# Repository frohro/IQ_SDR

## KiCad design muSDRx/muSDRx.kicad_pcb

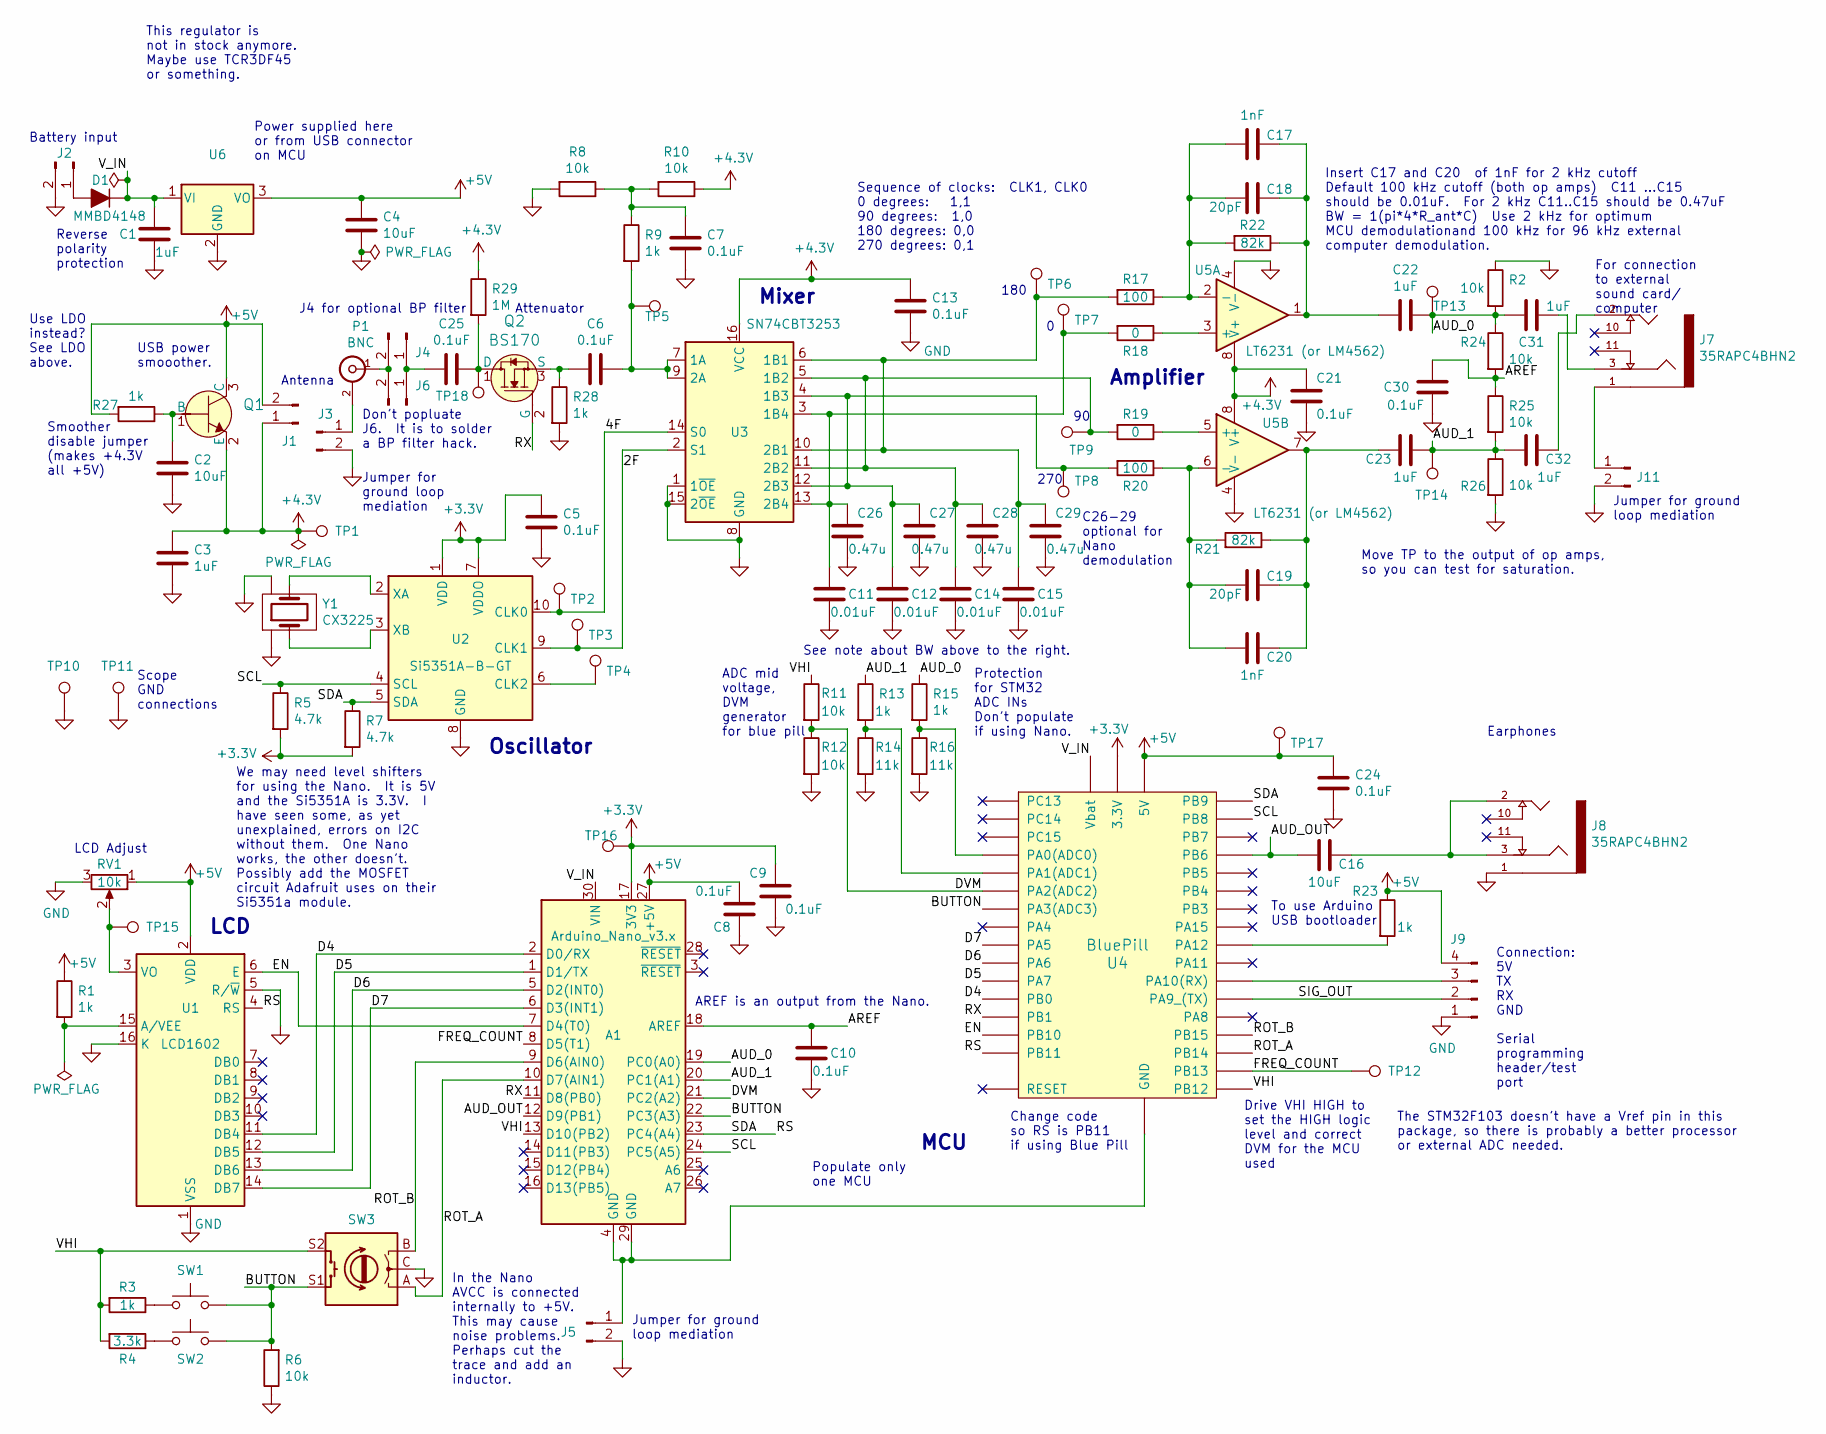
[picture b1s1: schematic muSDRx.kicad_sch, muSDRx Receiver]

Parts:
A1: Arduino_Nano_v3.x; Arduino_Nano
C1, C3, C22, C23: 1uF; C_0805
C2, C4, C16: 10uF; C_0805
C5, C6, C7, C8, C9, C10, C13, C21, C24: 0.1uF; C_0805
C11, C12, C14, C15: 0.01uF; C_0805
C17, C20: 1nF; C_0805_2012Metric
C18, C19: 20pF; C_0805
C25, C30: 0.1uF; C_0805_2012Metric
C26, C27, C28, C29: 0.47u; C_0805_2012Metric
C31, C32: 1uF; C_0805_2012Metric
D1: MMBD4148; D_SOT-23_ANK
J1, J2, J3, J4, J5, J6, J11: Conn_01x02_Male; Pin_Header_Straight_1x02_Pitch2.54mm
J7, J8: 35RAPC4BHN2; SWITCHCRAFT_35RAPC4BHN2
J9: Conn_01x04_Male; Pin_Header_Straight_1x04_Pitch2.54mm
P1: BNC; BNC_Socket_TYCO-AMP_LargePads
Q1: MMBT2222A-TP; SOT-23-3; MPN MMBT2222A-TP; Digi-Key_PN MMBT2222ATPMSCT-ND
Q2: BS170; TO-92-3; MPN BS170; Digi-Key_PN BS170-ND
R1, R3, R9, R13, R15, R23: 1k; R_0805
R2, R24, R25, R26: 10k; R_0805_2012Metric
R4: 3.3k; R_0805
R5, R7: 4.7k; R_0805
R6, R8, R10, R11, R12: 10k; R_0805
R14, R16: 11k; R_0805
R17, R20: 100; R_0805
R18, R19: 0; R_0805
R21, R22: 82k; R_0805
R27, R28: 1k; R_0805_2012Metric
R29: 1M; R_0805_2012Metric
RV1: 10k; Potentiometer_Trimmer_ACP_CA6h_Vertical
SW1, SW2: SW_Push; SW_PUSH_6mm_h4.3mm
SW3: Rotary_Encoder_Switch; Rotary_Encoder_Switched_PEC11R
TP1, TP2, TP3, TP4, TP5, TP6, TP7, TP8, TP9, TP10, TP11, TP12, TP13, TP14, TP15, TP16, TP17: TestPoint; PINTST
TP18: TestPoint; TestPoint_THTPad_D1.5mm_Drill0.7mm
U1: LCD1602; Pin_Header_Straight_1x16_Pitch2.54mm
U2: Si5351A-B-GT; MSOP-10_3x3mm_Pitch0.5mm
U3: SN74CBT3253; SOIC-16_3.9x9.9mm_Pitch1.27mm
U4: BluePill; BLUEPILL
U5: LT6231 (or LM4562); SOIC-8_3.9x4.9mm_Pitch1.27mm
U6: (no value)
Y1: CX3225; Crystal_SMD_Abracon_ABM8G-4pin_3.2x2.5mm

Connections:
+3V3: A1.17 (3V3), C5.1, C9.1, R5.2, R7.2, TP16.1, U2.1 (VDD), U2.7 (VDDO), U4.3V3 (3.3V)
+4.3V: C3.1, C13.1, C21.1, J1.1, Q1.2 (E), R10.1, R29.1, TP1.1, U3.16 (VCC), U5.8 (V+)
+5V: A1.27 (+5V), C4.1, C8.1, C24.1, J1.2, J9.4, Q1.3 (C), R1.1, R23.1, R27.2, RV1.1, TP17.1, U1.2 (VDD), U4.5V, U6.3 (VO)
/2F: TP3.1, U2.9 (CLK1), U3.2 (S1)
/4F: TP2.1, U2.10 (CLK0), U3.14 (S0)
/AREF: A1.18 (AREF), C10.1, C30.2, R24.2, R25.1
/AUD_0: A1.19 (PC0(A0)), C22.1, C31.1, R2.2, R15.1, R24.1, TP13.1
/AUD_1: A1.20 (PC1(A1)), C23.1, C32.1, R13.1, R25.2, R26.1, TP14.1
/AUD_OUT: A1.12 (D9(PB1)), C16.2, U4.PB6
/BUTTON: A1.22 (PC3(A3)), R6.2, SW1.2, SW2.2, SW3.S1, U4.PA3 (PA3(ADC3))
/D4: A1.2 (D0/RX), U1.11 (DB4), U4.PB0
/D5: A1.1 (D1/TX), U1.12 (DB5), U4.PA7
/D6: A1.5 (D2(INT0)), U1.13 (DB6), U4.PA6
/D7: A1.6 (D3(INT1)), U1.14 (DB7), U4.PA5
/DVM: A1.21 (PC2(A2)), R11.2, R12.1, U4.PA2 (PA2(ADC2))
/EN: A1.7 (D4(T0)), U1.6 (E), U4.PB10
/FREQ_COUNT: A1.8 (D5(T1)), TP12.1, U4.PB13
/ROT_A: A1.10 (D7(AIN1)), SW3.A, U4.PB14
/ROT_B: A1.9 (D6(AIN0)), SW3.B, U4.PB15
/RS: A1.23 (PC4(A4)), R7.1, U1.4 (RS), U2.5 (SDA), U4.PB9, U4.PB11
/RX: A1.11 (D8(PB0)), Q2.2 (G), U4.PB1
/SCL: A1.24 (PC5(A5)), R5.1, U2.4 (SCL), U4.PB8
/SIG_OUT: J9.2, U4.PA9 (PA9_(TX))
/VHI: A1.13 (D10(PB2)), R3.2, R4.2, R11.1, SW3.S2, U4.PB12
/V_IN: A1.30 (VIN), C1.1, D1.3 (K), U4.VBAT (Vbat), U6.1 (VI)
GND: C1.2, C2.2, C3.2, C4.2, C5.2, C7.2, C8.2, C9.2, C10.2, C11.2, C12.2, C13.2, C14.2, C15.2, C21.2, C24.2, C26.2, C27.2, C28.2, C29.2, C30.1, J2.2, J3.2, J5.2, J8.1, J9.1, J11.2, R2.1, R6.1, R8.2, R12.2, R14.2, R16.2, R26.2, R28.2, RV1.3, SW3.C, TP10.1, TP11.1, U1.1 (VSS), U1.5 (R/~W), U1.16 (K), U2.8 (GND), U3.1 (1~OE), U3.8 (GND), U3.15 (2~OE), U5.4 (V-), U6.2 (GND), Y1.2 (GND), Y1.4 (GND)
unnamed: A1.4 (GND), A1.29 (GND), J5.1, U4.G (GND)
unnamed: C2.1, Q1.1 (B), R27.1
unnamed: C6.1, R9.2, TP5.1, U3.7 (1A), U3.9 (2A)
unnamed: C6.2, Q2.3 (S), R28.1
unnamed: C7.1, R8.1, R9.1, R10.2
unnamed: C11.1, C26.1, R18.2, TP7.1, U3.3 (1B4), U3.13 (2B4)
unnamed: C12.1, C27.1, R20.2, TP8.1, U3.4 (1B3), U3.12 (2B3)
unnamed: C14.1, C28.1, R19.2, TP9.1, U3.5 (1B2), U3.11 (2B2)
unnamed: C15.1, C29.1, R17.2, TP6.1, U3.6 (1B1), U3.10 (2B1)
unnamed: C16.1, J8.2, J8.3
unnamed: C17.1, C18.1, C22.2, R22.1, U5.1
unnamed: C17.2, C18.2, R17.1, R22.2, U5.2 (-)
unnamed: C19.1, C20.1, C23.2, R21.1, U5.7
unnamed: C19.2, C20.2, R20.1, R21.2, U5.6 (-)
unnamed: C25.1, Q2.1 (D), R29.2, TP18.1
unnamed: C25.2, J4.1, J6.1
unnamed: C31.2, J7.3
unnamed: C32.2, J7.2
unnamed: D1.1 (A), J2.1
unnamed: J3.1, P1.2 (Ext)
unnamed: J4.2, J6.2, P1.1 (In)
unnamed: J9.3, U4.PA10 (PA10(RX))
unnamed: J7.1, J11.1
unnamed: R1.2, U1.15 (A/VEE)
unnamed: R3.1, SW1.1
unnamed: R4.1, SW2.1
unnamed: R13.2, R14.1, U4.PA1 (PA1(ADC1))
unnamed: R15.2, R16.1, U4.PA0 (PA0(ADC0))
unnamed: R18.1, U5.3 (+)
unnamed: R19.1, U5.5 (+)
unnamed: R23.2, U4.PA12
unnamed: RV1.2, TP15.1, U1.3 (VO)
unnamed: TP4.1, U2.6 (CLK2)
unnamed: U2.2 (XA), Y1.3 (2)
unnamed: U2.3 (XB), Y1.1

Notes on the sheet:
Power supplied here or from USB connector on MCU
Jumper for ground loop mediation
Reverse polarity protection
J4 for optional BP filter
Scope GND connections
Earphones
ADC mid voltage, DVM generator for blue pill
180
Populate only one MCU
Serial programming header/test port
C26-29 optional for Nano demodulation
Attenuator
Don't popluate J6. It is to solder a BP filter hack.
Mixer
Battery input
Amplifier
270
Jumper for ground loop mediation
USB power smooother.
Change code so RS is PB11 if using Blue Pill
Sequence of clocks: CLK1, CLK0 0 degrees: 1,1 90 degrees: 1,0 180 degrees: 0,0 270 degrees: 0,1
Use LDO instead? See LDO above.
Antenna
For connection to external sound card/ computer
See note about BW above to the right.
This regulator is not in stock anymore. Maybe use TCR3DF45 or something.
Move TP to the output of op amps, so you can test for saturation.
LCD
In the Nano AVCC is connected internally to +5V. This may cause noise problems. Perhaps cut the trace and add an inductor.
To use Arduino USB bootloader
Smoother disable jumper (makes +4.3V all +5V)
The STM32F103 doesn't have a Vref pin in this package, so there is probably a better processor or external ADC needed.
Protection for STM32 ADC INs Don't populate if using Nano.
AREF is an output from the Nano.
Insert C17 and C20 of 1nF for 2 kHz cutoff Default 100 kHz cutoff (both op amps) C11 ...C15 should be 0.01uF. For 2 kHz C11..C15 should be 0.47uF BW = 1(pi*4*R_ant*C) Use 2 kHz for optimum MCU demodulationand 100 kHz for 96 kHz external computer demodulation.
MCU
Oscillator
Drive VHI HIGH to set the HIGH logic level and correct DVM for the MCU used
We may need level shifters for using the Nano. It is 5V and the Si5351A is 3.3V. I have seen some, as yet unexplained, errors on I2C without them. One Nano works, the other doesn't. Possibly add the MOSFET circuit Adafruit uses on their Si5351a module.
LCD Adjust

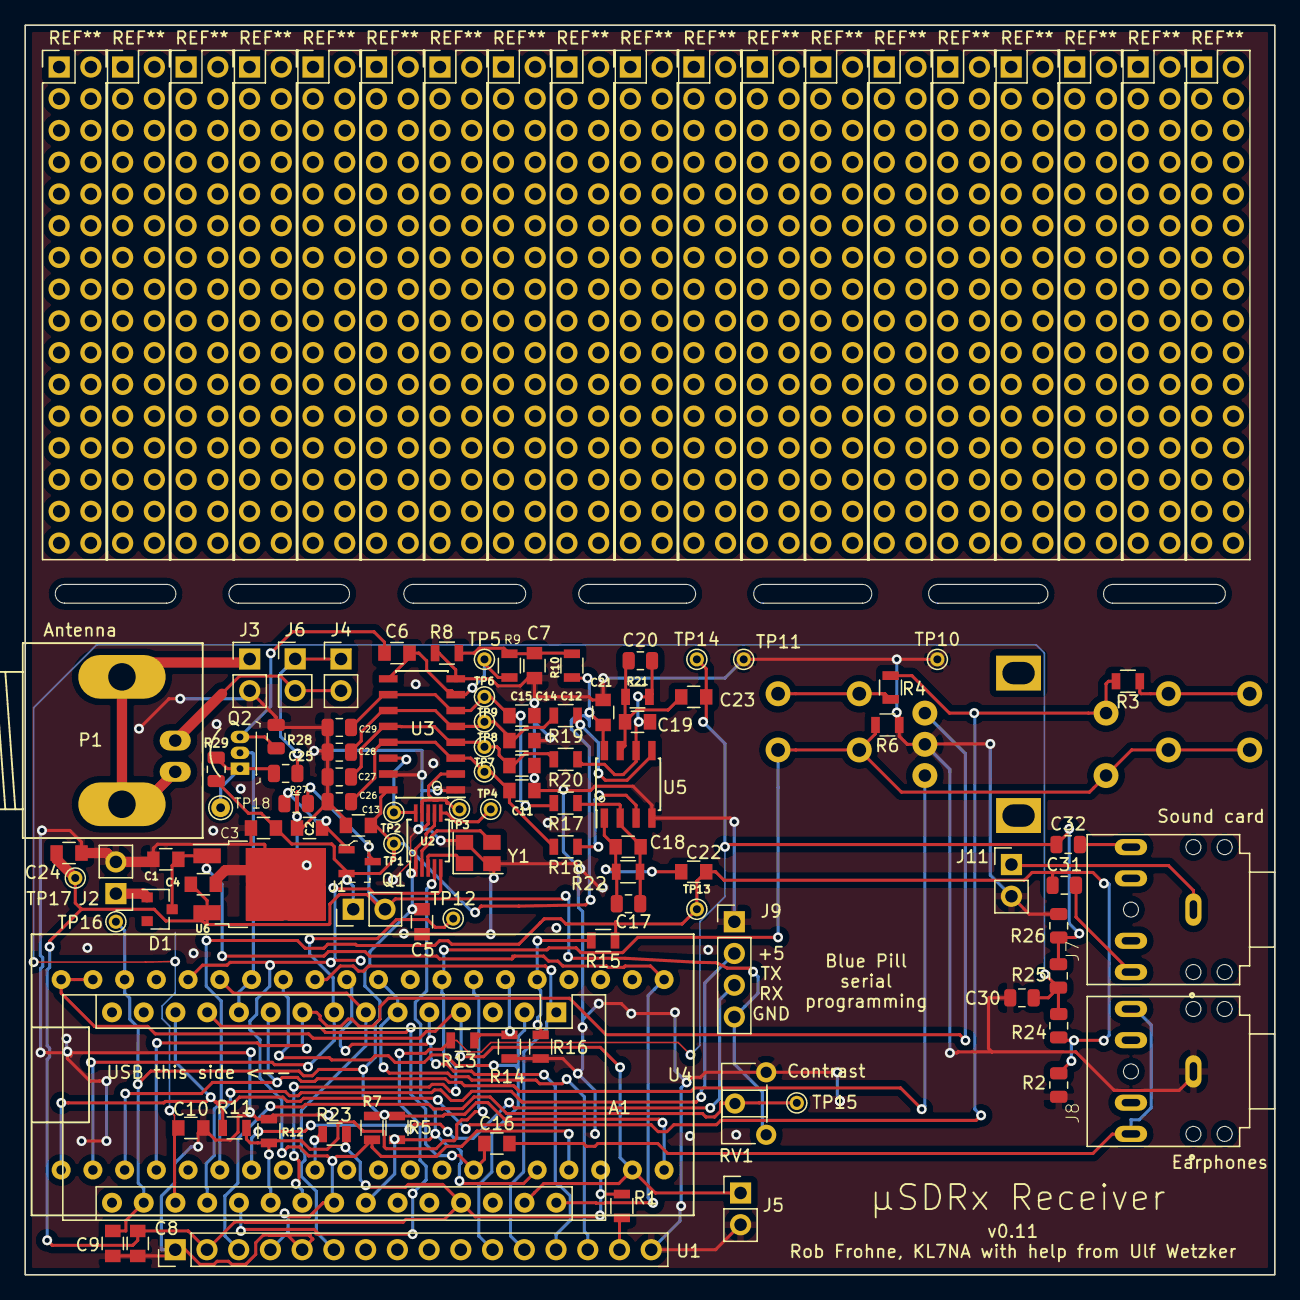
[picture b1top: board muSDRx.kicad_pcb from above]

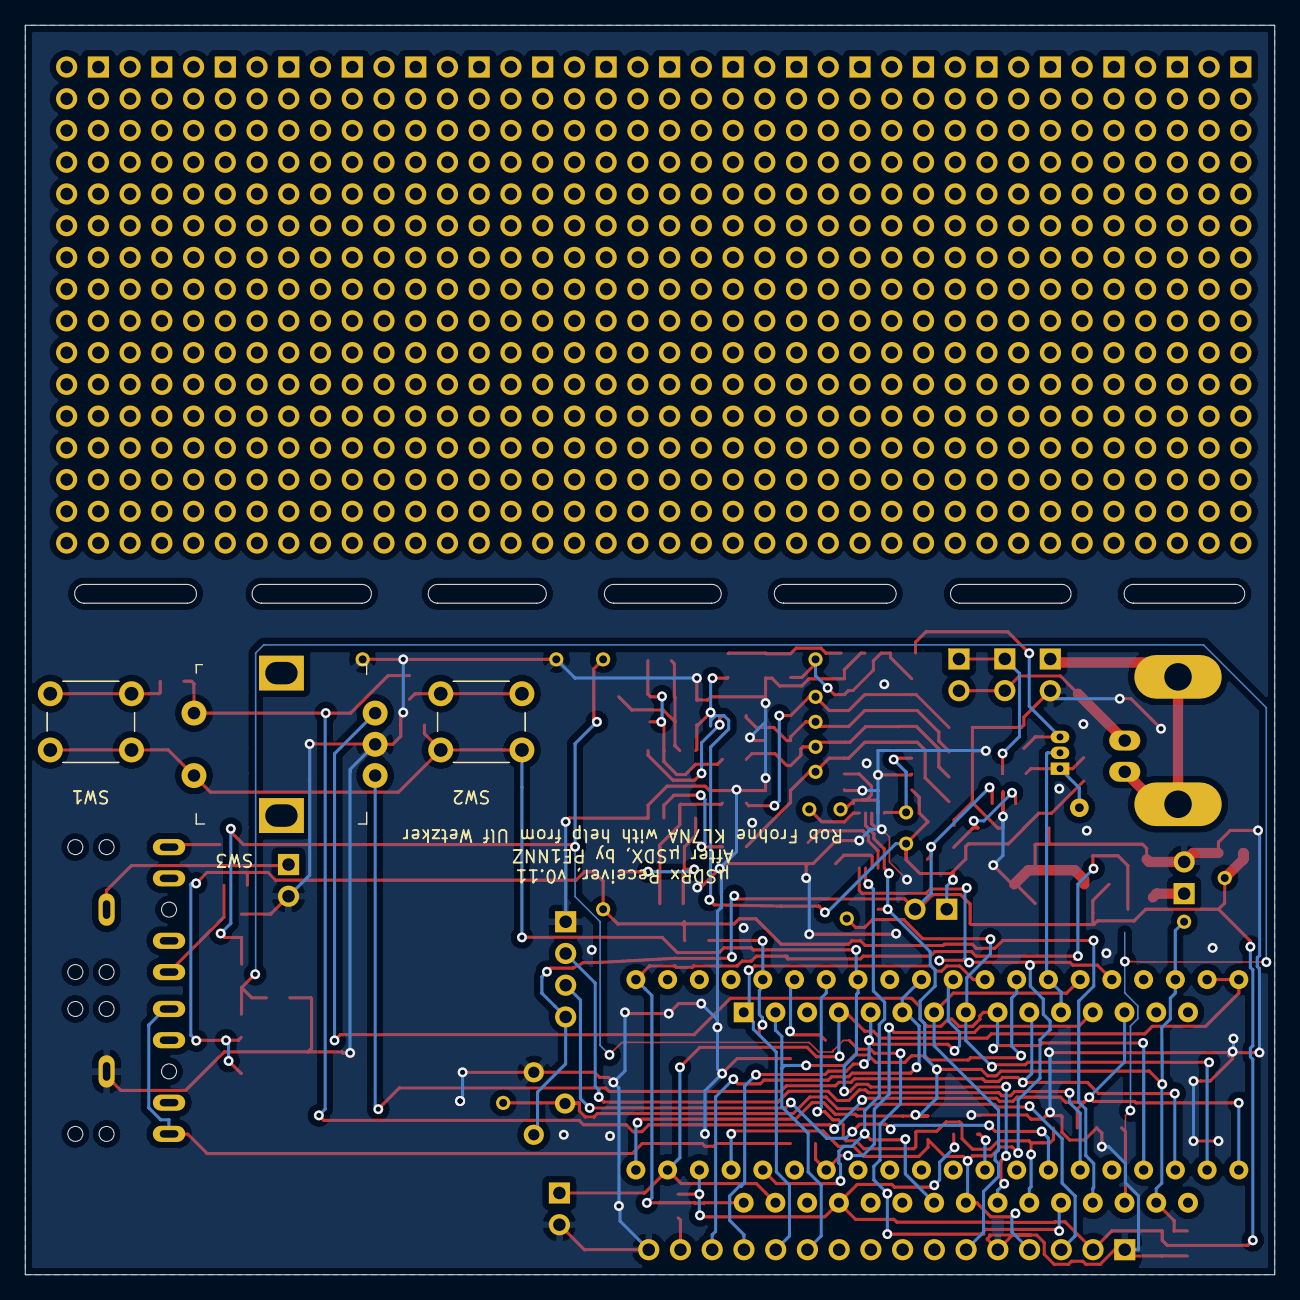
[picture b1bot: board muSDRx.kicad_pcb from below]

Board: 2 copper layers, 100.0 x 100.0 mm, 105 parts (3 on the bottom side), 61 nets.

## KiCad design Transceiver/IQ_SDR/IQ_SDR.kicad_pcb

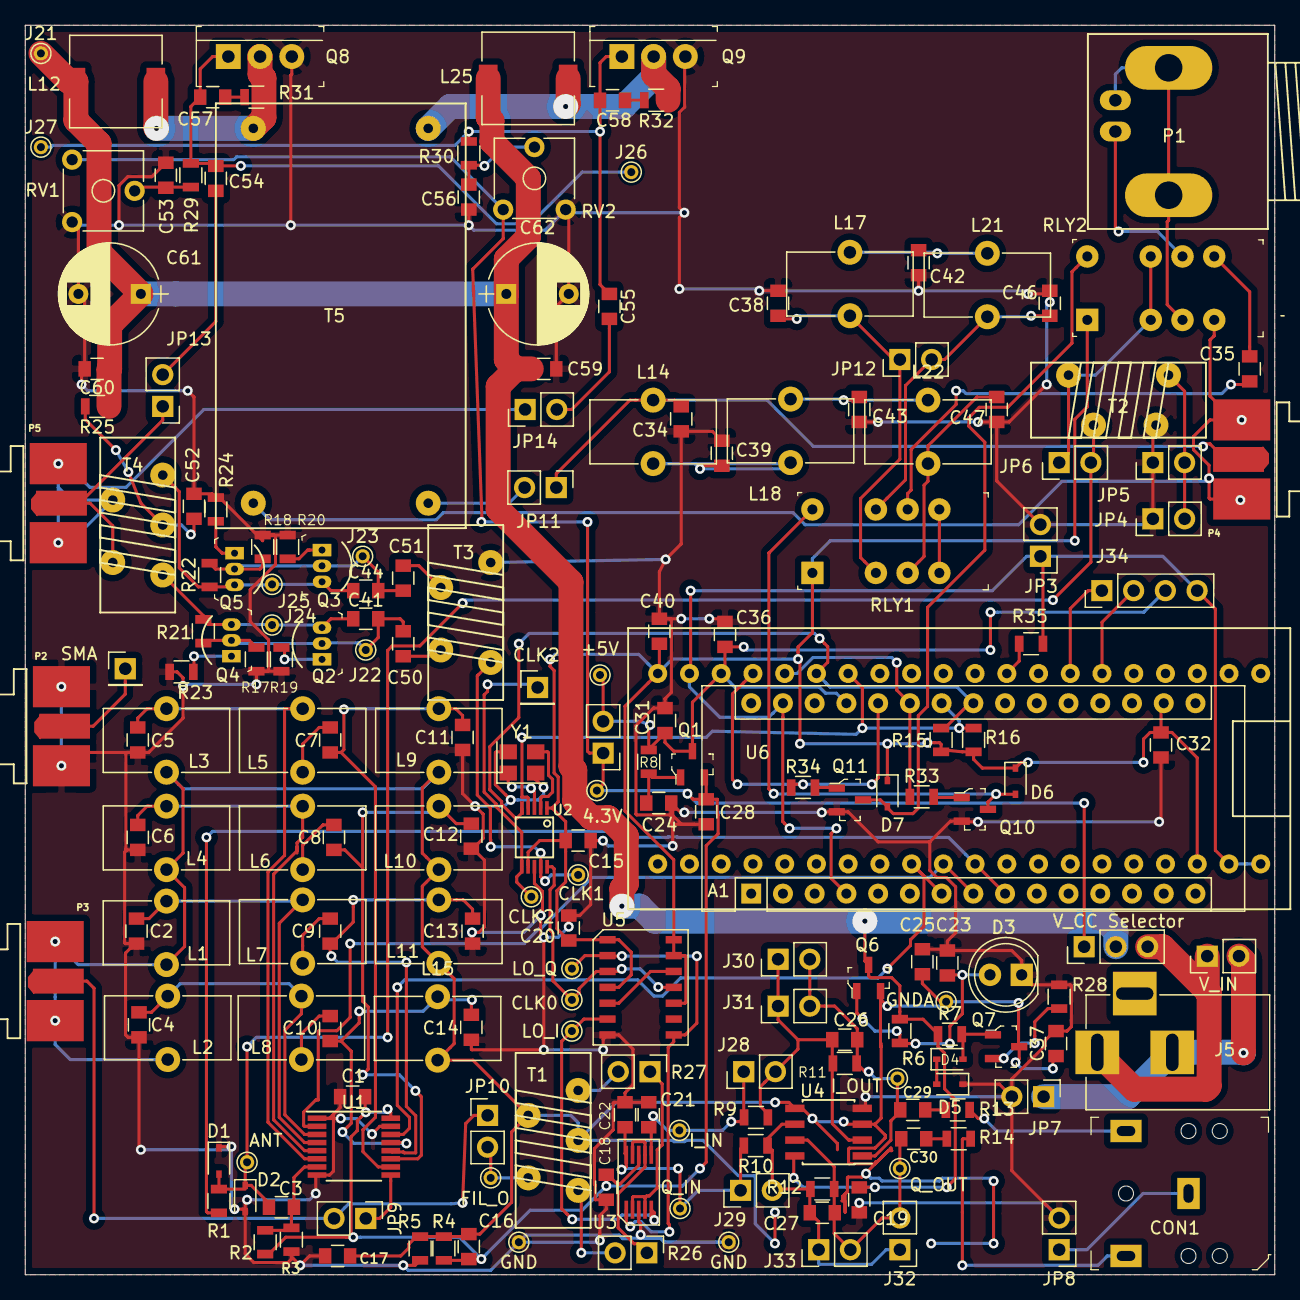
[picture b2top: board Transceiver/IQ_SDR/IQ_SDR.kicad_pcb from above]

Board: 2 copper layers, 100.0 x 100.0 mm, 201 parts (0 on the bottom side), 108 nets.

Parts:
A1: Arduino_Nano_v3.x; Arduino_Nano
C1, C18, C19: 0.01; C_0805
C2, C13: 820pF; C_0805
C3, C15, C16, C17, C20, C25, C28, C32, C40, C50, C51, C52, C53, C54, C55, C56, C57, C58, C59, C60: 0.1uF; C_0805
C4, C14: 1.5nF; C_0805
C5, C11, C41, C44: 220pF; C_0805
C6, C12: 390pF; C_0805
C7: 47pF; C_0805
C8: 100pF; C_0805
C9, C46: 180pF; C_0805
C10: 470pF; C_0805
C21, C22: 0.02uF; C_0805
C23, C24, C29, C30, C31, C36: 10uF; C_0805
C26, C27: 50pF; C_0805
C34, C47: 82pF; C_0805
C35: 1uF; C_0805
C37: 1u; C_0805
C38: 510pF; C_0805
C39, C43: 330pF; C_0805
C42: 680pF; C_0805
C61, C62: 470uF; CP_Radial_D8.0mm_P5.00mm
CON1: SJ1-3523N; Headphone_Jack_2.5mm_SJ1-3523N
D1, D2, D4, D5, D6, D7: 1N914; D_SOD-323
D3: LED_Solid; LED_D5.0mm
J1: ANT; PINTST
J2, J4: GND; PINTST
J3: V_IN; Pin_Header_Straight_1x02_Pitch2.54mm
J5: V_IN; BARREL_JACK
J6: FIL_O; PINTST
J7: CLK1; PINTST
J8: CLK2; PINTST
J9: CLK0; PINTST
J10: LO_I; PINTST
J11: LO_Q; PINTST
J12: GNDA; PINTST
J13: I_IN; PINTST
J14: Q_IN; PINTST
J15: +5V; PINTST
J16: 4.3V; PINTST
J17: I_OUT; PINTST
J18: Q_OUT; PINTST
J19: CLK2; Pin_Header_Straight_1x01_Pitch2.54mm
J20: SMA; Pin_Header_Straight_1x01_Pitch2.54mm
J21: V_CC; PINTST
J22: Ba; PINTST
J23: Bb; PINTST
J24: Cb; PINTST
J25: Ca; PINTST
J26: Gb; PINTST
J27: Ga; PINTST
J28, J29, J30, J31, J32, J33: Conn_01x02_Female; Socket_Strip_Straight_1x02_Pitch2.54mm
J34: Conn_01x04_Male; Pin_Header_Straight_1x04_Pitch2.54mm
JP1: smooth disable; Pin_Header_Straight_1x02_Pitch2.54mm
JP2: V_CC Selector; Pin_Header_Straight_1x03_Pitch2.54mm
JP3: Ground loop mitigation for the Arduino; Pin_Header_Straight_1x02_Pitch2.54mm
JP4: Ground loop mitigation for the RX antenna; Pin_Header_Straight_1x02_Pitch2.54mm
JP5, JP6: T2 bypass; Pin_Header_Straight_1x02_Pitch2.54mm
JP7: V_IN ground loop mitigation; Pin_Header_Straight_1x02_Pitch2.54mm
JP8: Ground loop mitigation for audio; Pin_Header_Straight_1x02_Pitch2.54mm
JP9: BP_1; Pin_Header_Straight_1x02_Pitch2.54mm
JP10: BP_2; Pin_Header_Straight_1x02_Pitch2.54mm
JP11: Tx filter disconnect; Pin_Header_Straight_1x02_Pitch2.54mm
JP12: 40m Filter Bypass; Pin_Header_Straight_1x02_Pitch2.54mm
JP13, JP14: QRP; Pin_Header_Straight_1x02_Pitch2.54mm
L1: 1uH; L_Toroid_Vertical_L10.0mm_W5.0mm_P5.08mm
L2, L15: 2.4uH; L_Toroid_Vertical_L10.0mm_W5.0mm_P5.08mm
L3: 232nH; L_Toroid_Vertical_L10.0mm_W5.0mm_P5.08mm
L4: 497nH; L_Toroid_Vertical_L10.0mm_W5.0mm_P5.08mm
L5: 1.137uH; L_Toroid_Vertical_L10.0mm_W5.0mm_P5.08mm
L6: 1.98uH; L_Toroid_Vertical_L10.0mm_W5.0mm_P5.08mm
L7: 4uH; L_Toroid_Vertical_L10.0mm_W5.0mm_P5.08mm
L8: 7.2uH; L_Toroid_Vertical_L10.0mm_W5.0mm_P5.08mm
L9: 256nH; L_Toroid_Vertical_L10.0mm_W5.0mm_P5.08mm
L10: 626nH; L_Toroid_Vertical_L10.0mm_W5.0mm_P5.08mm
L11, L17: 1.7uH; L_Toroid_Vertical_L10.0mm_W5.0mm_P5.08mm
L12, L25: 300uH; L_7.3x7.3_H4.5
L14, L22: 590nH; L_Toroid_Vertical_L10.0mm_W5.0mm_P5.08mm
L18: 910nH; L_Toroid_Vertical_L10.0mm_W5.0mm_P5.08mm
L21: 1.24uH; L_Toroid_Vertical_L10.0mm_W5.0mm_P5.08mm
P1: BNC; BNC_Socket_TYCO-AMP_LargePads
P2, P3, P4, P5: SMA; SMA_EDGE
Q1, Q6, Q7, Q10, Q11: MMBT2222A-TP; SOT-23-3
Q2, Q3, Q4, Q5: 2N3904; TO-92-3
Q8, Q9: IRF510PBF; TO-220-3
R1: 2.2k; R_0805
R2, R4: 10k; R_0805
R3, R5: 5.6k; R_0805
R6: 2k; R_0805
R7: 27k; R_0805
R8, R21, R22: 1k; R_0805
R9, R10: 50; R_0805
R11, R12: 13k; R_0805
R13, R14, R17, R18: 100; R_0805
R15, R16, R33, R34: 4.7k; R_0805
R19, R20, R23, R24: 22; R_0805
R25: 2.2; R_0805
R26, R27: 0; Socket_Strip_Straight_1x02_Pitch2.54mm
R28: 500; R_0805
R29, R30: 47; R_0805
R31, R32: 220; R_0805
R35: 1.6k; R_0805
RLY1, RLY2: TX2SA-L-3V-Z
RV1, RV2: 10k; Potentiometer_Trimmer_ACP_CA6v_Horizontal
T1: Transformer_1P_SS; T50-2_vertical_5_pin
T2, T3: Transformer_1P_1S; T50-2_vertical_4_pin
T4: Transformer_SP_1S; T50-2_vertical_5_pin
T5: BN43-6802
U1: FST3253 or TS3A5017; TSSOP-16_4.4x5mm_Pitch0.65mm
U2: Si5351A-B-GT; MSOP-10
U3: TS5A23157; DGS0010A
U4: LM4562 or LT6231; SOIC-8_3.9x4.9mm_Pitch1.27mm
U5: 74ALVC74D; SO14
U6: Blue Pill; BLUEPILL
Y1: CX3225; Crystal_SMD_Abracon_ABM8G-4pin_3.2x2.5mm

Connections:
+3V3: A1.17, C15.1, C20.1, C32.1, C40.1, D6.1, D7.1, R15.2, R16.2, RLY1.1, RLY2.1, U2.1, U2.7, U5.1, U5.4, U5.10, U5.13, U5.14, U6.3V3
+4.3V: C1.1, C16.1, C18.1, C28.1, J16.1, JP1.1, JP2.1, Q1.2, R2.2, R4.2, RV1.3, RV2.3, U1.16, U3.8
+5V: A1.27, C31.1, C36.1, J15.1, J34.3, JP1.2, Q1.3, R8.1, U6.5V
/ANT_RLY: A1.26, R34.1, U6.PB9
/B0: A1.7, U1.14, U6.PA4
/B1: A1.8, U1.2, U6.PA5
/D_GND: A1.4, A1.29, J34.4, JP3.1, R35.2, U6.G
/LO_I: J10.1, U3.5, U5.6
/LO_Q: J11.1, U3.1, U5.2, U5.8
/MUTE: A1.9, R1.2, U6.PA6
/PA_V_CCb: L12.1, Q8.2, R31.1, T5.1
/PA_V_CCc: L25.1, Q9.2, R32.1, T5.2
/RFa: P4.2, RLY2.5, T5.3
/RFb: P1.2, RLY2.4
/RFc: C35.2, RLY1.9
/RFd: C47.1, L22.2, RLY1.4
/RFf: C39.1, L14.2, L18.1
/RFg: C38.1, JP12.1, L17.1, RLY1.3
/RFh: C46.1, JP12.2, L21.2, RLY1.10
/RFj: C43.1, L18.2, L22.1
/RFk: C42.1, L17.2, L21.1
/RFm: P1.1, RLY2.9
/RX_ANT_+: JP6.1, RLY2.3, RLY2.10, T2.1
/RX_ANT_-: JP4.2, JP5.2, T2.2
/Rfe: C34.1, JP11.1, L14.1, P4.1
/SCL: A1.24, R16.1, U2.4, U6.PB6
/SDA: A1.23, R15.1, U2.5, U6.PB7
/TX_BAND: A1.25, R33.1, U6.PB8
GND: C1.2, C2.2, C4.2, C5.2, C6.2, C11.2, C12.2, C13.2, C14.2, C15.2, C17.2, C18.2, C19.2, C20.2, C21.2, C22.2, C23.1, C24.2, C25.1, C28.2, C31.2, C32.2, C34.2, C36.2, C37.2, C38.2, C39.2, C40.2, C42.2, C43.2, C46.2, C47.2, C52.2, C53.2, C56.2, C59.2, C60.2, C61.2, C62.2, D1.1, D2.2, D3.1, D5.1, J2.1, J4.1, JP3.2, JP4.1, JP5.1, JP7.2, JP8.2, P2.2, Q8.3, Q9.3, Q10.2, Q11.2, R3.1, R5.1, R17.2, R18.2, R19.2, R20.2, R23.2, R24.2, R28.2, RV1.1, RV2.1, T2.3, T3.1, U1.1, U1.8, U1.15, U2.8, U3.3, U4.4, U5.7, Y1.2, Y1.4
GNDA: C16.2, C17.1, C25.2, C37.1, J12.1, L1.2, L2.2, L3.2, L4.2, L9.2, L10.2, L11.2, L15.2, P3.2, Q6.2, Q7.3, R4.1, R5.2, T1.1, T1.4, U4.3, U4.5
unnamed: C2.1, L1.1, L7.1, U1.4
unnamed: C3.1, D1.2, D2.1, J1.1, JP6.2, R1.1, T2.4
unnamed: C3.2, R2.1, R3.2, U1.7
unnamed: C4.1, L2.1, L8.1, U1.3
unnamed: C5.1, L3.1, L5.1, U1.6
unnamed: C6.1, L4.1, L6.1, U1.5
unnamed: C7.2, L5.2
unnamed: C8.2, L6.2
unnamed: C9.2, L7.2
unnamed: C10.1, C14.1, L15.1, U1.13
unnamed: C10.2, L8.2
unnamed: C7.1, C11.1, L9.1, U1.10
unnamed: C8.1, C12.1, L10.1, U1.11
unnamed: C9.1, C13.1, L11.1, U1.12
unnamed: C21.1, J13.1, J28.1, R9.2, U3.6
unnamed: C22.1, J14.1, J29.1, R10.2, U3.10
unnamed: C23.2, D3.2, Q6.1, R6.2
unnamed: C24.1, Q1.1, R8.2
unnamed: C26.1, C29.2, J17.1, J30.2, J31.2, R11.1, U4.1
unnamed: C26.2, J28.2, J30.1, J31.1, R9.1, R11.2, U4.2
unnamed: C27.1, C30.2, J18.1, J32.2, J33.2, R12.1, U4.7
unnamed: C27.2, J29.2, J32.1, J33.1, R10.1, R12.2, U4.6
unnamed: C29.1, R13.2
unnamed: C30.1, R14.2
unnamed: C35.1, RLY2.8
unnamed: C41.1, J24.1, Q2.3, Q4.3, R21.1, T4.3
unnamed: C41.2, C50.1, J22.1, Q2.2, Q4.2, R17.1, R21.2
unnamed: C44.1, J25.1, Q3.3, Q5.3, R22.1, T4.1
unnamed: C44.2, C51.1, J23.1, Q3.2, Q5.2, R18.1, R22.2
unnamed: C50.2, T3.3
unnamed: C51.2, T3.4
unnamed: C52.1, R25.2, T4.2
unnamed: C53.1, R29.1, RV1.2
unnamed: C54.1, C57.1, J26.1, Q8.1, R29.2
unnamed: C54.2, JP13.2
unnamed: C55.1, C58.1, J27.1, Q9.1, R30.2
unnamed: C55.2, JP14.2
unnamed: C56.1, R30.1, RV2.2
unnamed: C57.2, R31.2
unnamed: C58.2, R32.2
unnamed: CON1.1, JP8.1
unnamed: CON1.2, R13.1
unnamed: CON1.3, R14.1
unnamed: D4.1, D5.2
unnamed: D4.2, Q7.1, R7.2
unnamed: D6.2, Q10.3, RLY1.12
unnamed: D7.2, Q11.3, RLY2.12
unnamed: J3.2, J5.2, JP7.1
unnamed: J6.1, JP10.2, T1.2
unnamed: J7.1, T3.2, U2.9
unnamed: J9.1, U2.10, U5.3, U5.11
unnamed: J8.1, J19.1, U2.6
unnamed: J20.1, P2.1
unnamed: J34.1, U6.PA10
unnamed: J34.2, U6.PA9
unnamed: JP9.1, U1.9
unnamed: JP9.2, JP10.1, P3.1
unnamed: JP11.2, T5.4
unnamed: JP13.1, P5.1, T4.4
unnamed: JP14.1, P5.2, T4.5
unnamed: Q2.1, R19.1
unnamed: Q3.1, R20.1
unnamed: Q4.1, R23.1
unnamed: Q5.1, R24.1
unnamed: Q7.2, R28.1
unnamed: Q10.1, R33.2
unnamed: Q11.1, R34.2
unnamed: R26.1, U3.7, U3.9
unnamed: R26.2, T1.3
unnamed: R27.1, U3.2, U3.4
unnamed: R27.2, T1.5
unnamed: R35.1, U6.PA12
unnamed: RLY1.5, RLY1.8
unnamed: U2.2, Y1.3
unnamed: U2.3, Y1.1
unnamed: U5.5, U5.12
V_CC: C19.1, C59.1, C60.1, C61.1, C62.1, J21.1, JP2.2, L12.2, L25.2, Q6.3, R6.1, R7.1, R25.1, U4.8
V_IN: J3.1, J5.1, JP2.3

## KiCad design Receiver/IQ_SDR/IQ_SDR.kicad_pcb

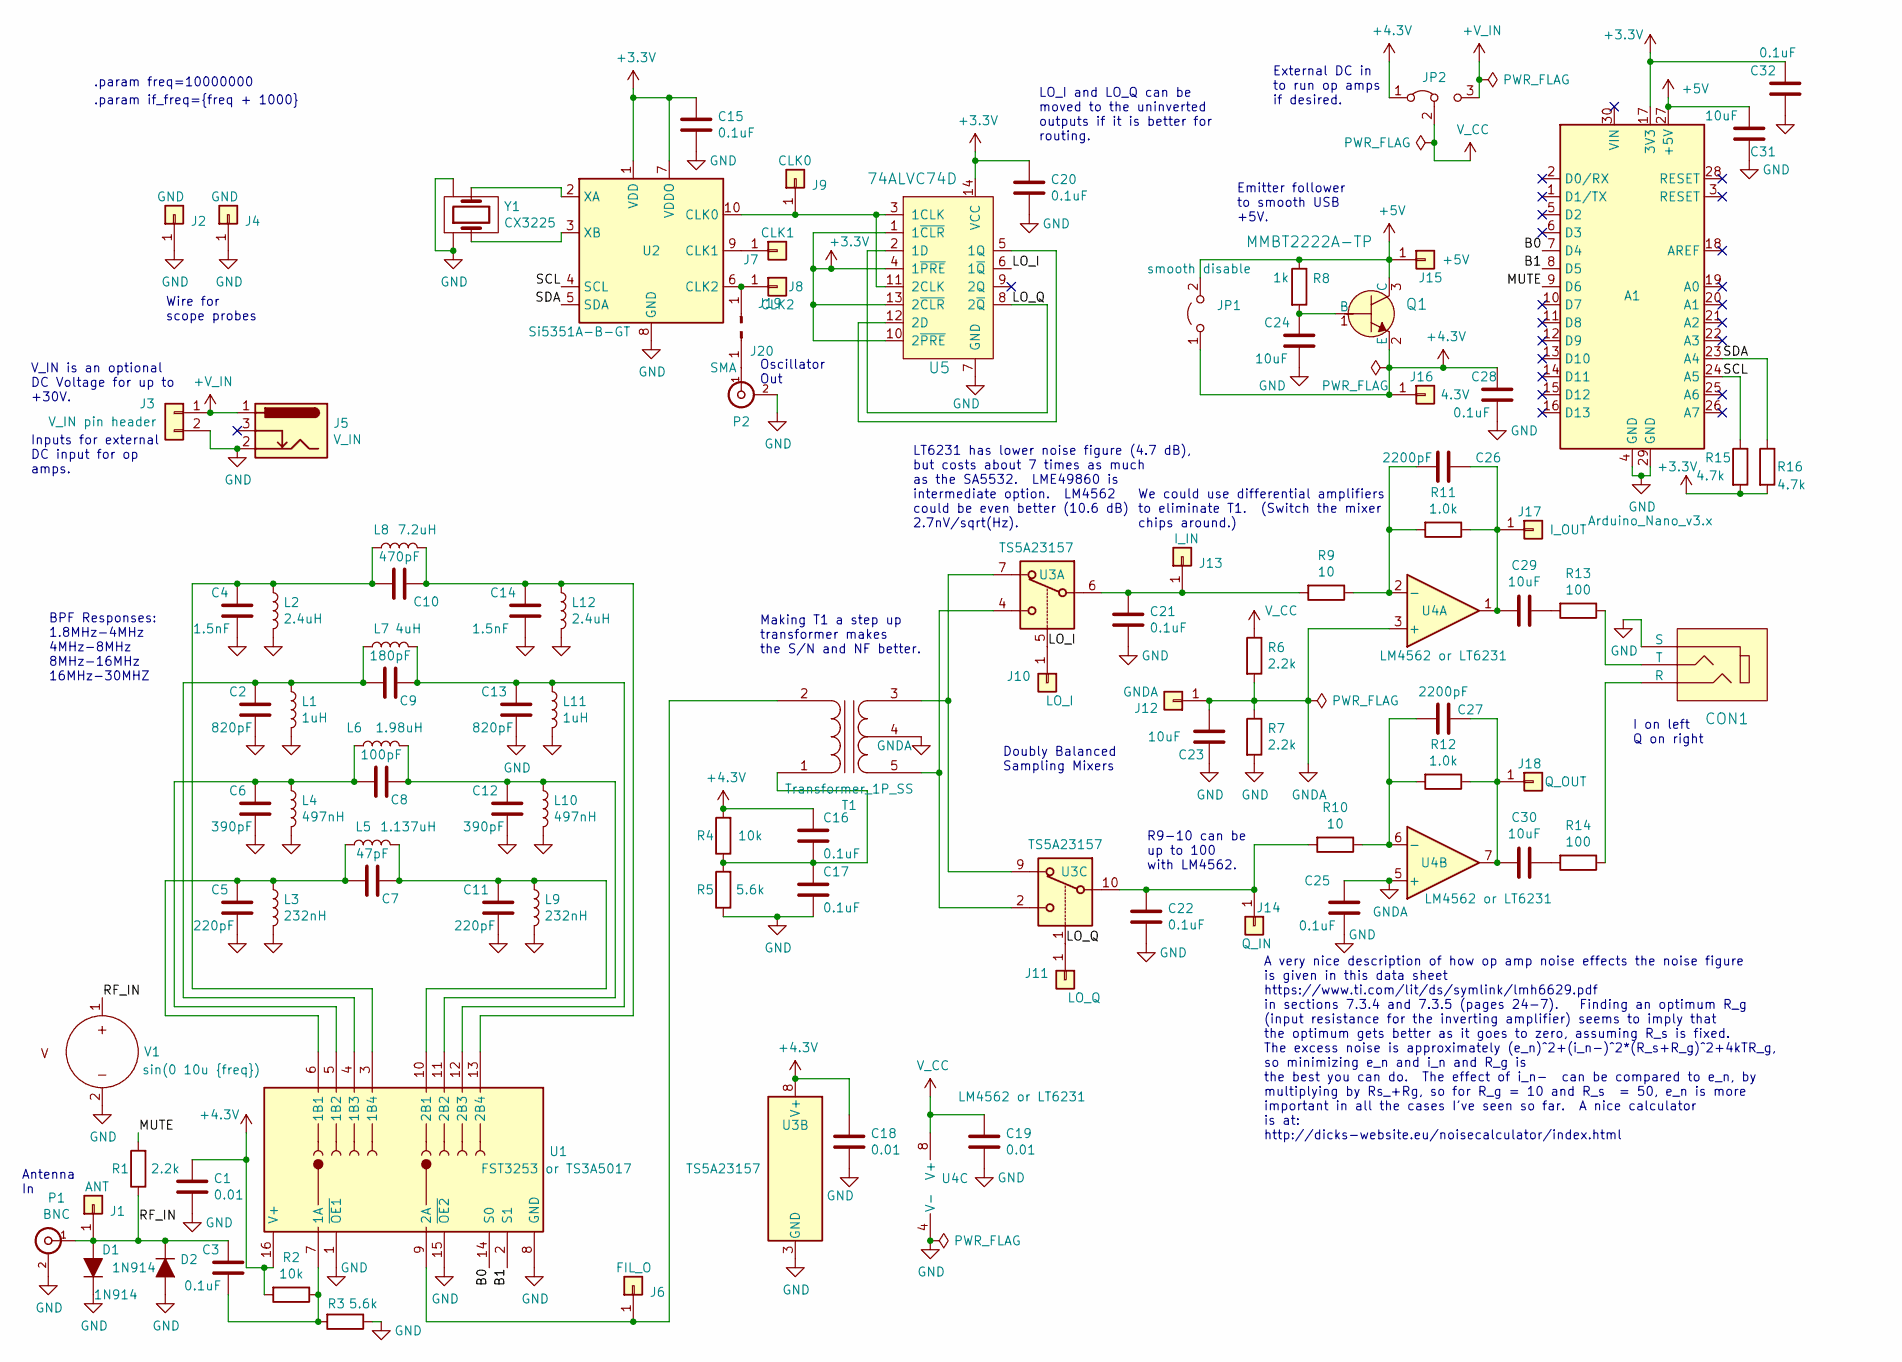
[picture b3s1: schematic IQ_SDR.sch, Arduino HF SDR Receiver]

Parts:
A1: Arduino_Nano_v3.x; Arduino_Nano
C1, C18, C19: 0.01; C_0805
C2, C13: 820pF; C_0805
C3, C15, C16, C17, C20, C21, C22, C25, C28, C32: 0.1uF; C_0805
C4, C14: 1.5nF; C_0805
C5, C11: 220pF; C_0805
C6, C12: 390pF; C_0805
C7: 47pF; C_0805
C8: 100pF; C_0805
C9: 180pF; C_0805
C10: 470pF; C_0805
C23, C24, C29, C30, C31: 10uF; C_0805
C26, C27: 2200pF; C_0805
CON1: SJ1-3523N; Headphone_Jack_2.5mm_SJ1-3523N; MPN SJ1-3523N; Digi-Key_PN CP1-3523N-ND
D1, D2: 1N914; D_SOD-323
J1: ANT; PINTST
J2, J4: GND; PINTST
J3: V_IN pin header; Pin_Header_Straight_1x02_Pitch2.54mm
J5: V_IN; BARREL_JACK
J6: FIL_O; PINTST
J7: CLK1; PINTST
J8: CLK2; PINTST
J9: CLK0; PINTST
J10: LO_I; PINTST
J11: LO_Q; PINTST
J12: GNDA; PINTST
J13: I_IN; PINTST
J14: Q_IN; PINTST
J15: +5V; PINTST
J16: 4.3V; PINTST
J17: I_OUT; PINTST
J18: Q_OUT; PINTST
J19, J20: Conn_01x01_Male; Pin_Header_Straight_1x01_Pitch2.54mm
JP1: smooth disable; Pin_Header_Straight_1x02_Pitch2.54mm
JP2: Jumper_3_Bridged12; Pin_Header_Straight_1x03_Pitch2.54mm
L1, L11: 1uH; L_Toroid_Vertical_L10.0mm_W5.0mm_P5.08mm
L2, L12: 2.4uH; L_Toroid_Vertical_L10.0mm_W5.0mm_P5.08mm
L3, L9: 232nH; L_Toroid_Vertical_L10.0mm_W5.0mm_P5.08mm
L4, L10: 497nH; L_Toroid_Vertical_L10.0mm_W5.0mm_P5.08mm
L5: 1.137uH; L_Toroid_Vertical_L10.0mm_W5.0mm_P5.08mm
L6: 1.98uH; L_Toroid_Vertical_L10.0mm_W5.0mm_P5.08mm
L7: 4uH; L_Toroid_Vertical_L10.0mm_W5.0mm_P5.08mm
L8: 7.2uH; L_Toroid_Vertical_L10.0mm_W5.0mm_P5.08mm
P1: BNC; BNC_Socket_TYCO-AMP_LargePads
P2: SMA; SMA_EDGE
Q1: MMBT2222A-TP; SOT-23-3; MPN MMBT2222A-TP; Digi-Key_PN MMBT2222ATPMSCT-ND
R1, R6, R7: 2.2k; R_0805
R2, R4: 10k; R_0805
R3, R5: 5.6k; R_0805
R8: 1k; R_0805
R9, R10: 10; R_0805
R11, R12: 1.0k; R_0805
R13, R14: 100; R_0805
R15, R16: 4.7k; R_0805
T1: Transformer_1P_SS; 4_to_1_Transmission_Line_TransformerTHT
U1: FST3253 or TS3A5017; TSSOP-16_4.4x5mm_Pitch0.65mm
U2: Si5351A-B-GT; MSOP-10
U3: TS5A23157; DGS0010A
U4: LM4562 or LT6231; SOIC-8_3.9x4.9mm_Pitch1.27mm
U5: 74ALVC74D; SO14; MPN SN74HC74N; Digi-Key_PN 1727-6097-ND
V1: sin(0 10u {freq})
Y1: CX3225; Crystal_SMD_Abracon_ABM8G-4pin_3.2x2.5mm

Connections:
+3V3: A1.17 (3V3), C15.1, C20.1, C32.1, R15.2, R16.2, U2.1 (VDD), U2.7 (VDDO), U5.1 (1~CLR), U5.4 (1~PRE), U5.10 (2~PRE), U5.13 (2~CLR), U5.14 (VCC)
+4.3V: C1.1, C16.1, C18.1, C28.1, J16.1, JP1.1 (A), JP2.1 (A), Q1.2 (E), R2.2, R4.2, U1.16 (V+), U3.8 (V+)
+5V: A1.27 (+5V), C31.1, J15.1, JP1.2 (B), Q1.3 (C), R8.1
/B0: A1.7 (D4), U1.14 (S0)
/B1: A1.8 (D5), U1.2 (S1)
/LO_I: J10.1, U3.5, U5.6 (1~Q)
/LO_Q: J11.1, U3.1, U5.2 (1D), U5.8 (2~Q)
/MUTE: A1.9 (D6), R1.2
/RF_IN: C3.1, D1.2 (A), D2.1 (K), J1.1, P1.1 (In), R1.1, V1.1
/SCL: A1.24 (A5), R15.1, U2.4 (SCL)
/SDA: A1.23 (A4), R16.1, U2.5 (SDA)
GND: A1.4 (GND), A1.29 (GND), C1.2, C2.2, C4.2, C5.2, C6.2, C11.2, C12.2, C13.2, C14.2, C15.2, C17.2, C18.2, C19.2, C20.2, C21.2, C22.2, C23.1, C24.2, C25.1, C28.2, C31.2, C32.2, CON1.1 (S), D1.1 (K), D2.2 (A), J2.1, J3.2, J4.1, J5.2, L1.2, L2.2, L3.2, L4.2, L9.2, L10.2, L11.2, L12.2, P1.2 (Ext), P2.2 (Ext), R3.1, R5.1, R7.2, U1.1 (~OE1), U1.8 (GND), U1.15 (~OE2), U2.8 (GND), U3.3 (GND), U4.4 (V-), U5.7 (GND), V1.2, Y1.2 (GND), Y1.4 (GND)
GNDA: C23.2, C25.2, J12.1, R6.2, R7.1, T1.4 (SC), U4.3 (+), U4.5 (+)
unnamed: C2.1, C9.2, L1.1, L7.1, U1.4 (1B3)
unnamed: C3.2, R2.1, R3.2, U1.7 (1A)
unnamed: C5.1, C7.2, L3.1, L5.1, U1.6 (1B1)
unnamed: C6.1, C8.2, L4.1, L6.1, U1.5 (1B2)
unnamed: C10.1, C14.1, L8.2, L12.1, U1.13 (2B4)
unnamed: C4.1, C10.2, L2.1, L8.1, U1.3 (1B4)
unnamed: C7.1, C11.1, L5.2, L9.1, U1.10 (2B1)
unnamed: C8.1, C12.1, L6.2, L10.1, U1.11 (2B2)
unnamed: C9.1, C13.1, L7.2, L11.1, U1.12 (2B3)
unnamed: C16.2, C17.1, R4.1, R5.2, T1.1 (AA)
unnamed: C21.1, J13.1, R9.2, U3.6
unnamed: C22.1, J14.1, R10.2, U3.10
unnamed: C24.1, Q1.1 (B), R8.2
unnamed: C26.1, C29.2, J17.1, R11.1, U4.1
unnamed: C26.2, R9.1, R11.2, U4.2 (-)
unnamed: C27.1, C30.2, J18.1, R12.1, U4.7
unnamed: C27.2, R10.1, R12.2, U4.6 (-)
unnamed: C29.1, R13.2
unnamed: C30.1, R14.2
unnamed: CON1.2 (T), R13.1
unnamed: CON1.3 (R), R14.1
unnamed: J6.1, T1.2 (AB), U1.9 (2A)
unnamed: J7.1, U2.9 (CLK1)
unnamed: J9.1, U2.10 (CLK0), U5.3 (1CLK), U5.11 (2CLK)
unnamed: J8.1, J19.1, U2.6 (CLK2)
unnamed: J20.1, P2.1 (In)
unnamed: T1.3 (SA), U3.7, U3.9
unnamed: T1.5 (SB), U3.2, U3.4
unnamed: U2.2 (XA), Y1.3 (2)
unnamed: U2.3 (XB), Y1.1
unnamed: U5.5 (1Q), U5.12 (2D)
V_CC: C19.1, JP2.2 (C), R6.1, U4.8 (V+)
V_IN: J3.1, J5.1, JP2.3 (B)

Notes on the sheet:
Doubly Balanced Sampling Mixers
.param freq=10000000
.param if_freq={freq + 1000}
LO_I and LO_Q can be moved to the uninverted outputs if it is better for routing.
I on left Q on right
A very nice description of how op amp noise effects the noise figure is given in this data sheet https://www.ti.com/lit/ds/symlink/lmh6629.pdf in sections 7.3.4 and 7.3.5 (pages 24-7). Finding an optimum R_g (input resistance for the inverting amplifier) seems to imply that the optimum gets better 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
LT6231 has lower noise figure (4.7 dB), but costs about 7 times as much as the SA5532. LME49860 is intermediate option. LM4562 could be even better (10.6 dB) 2.7nV/sqrt(Hz).
Antenna In
Oscillator Out
Wire for scope probes
V_IN is an optional DC Voltage for up to +30V.
Emitter follower to smooth USB +5V.
External DC in to run op amps if desired.
Inputs for external DC input for op amps.
R9-10 can be up to 100 with LM4562.
Making T1 a step up transformer makes the S/N and NF better.
BPF Responses: 1.8MHz-4MHz 4MHz-8MHz 8MHz-16MHz 16MHz-30MHZ
We could use differential amplifiers to eliminate T1. (Switch the mixer chips around.)

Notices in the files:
Receiver/IQ_SDR/IQ_SDR.kicad_pcb:
Open Hardware License
